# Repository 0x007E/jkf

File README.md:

# `JKF` - JK FlipFlop Board

The `JKF` is a board with an [CD4027](#additional-information) or any other dual `JK-FlipFlop` that meets the pin requirements. The board itself can be driven from `5` to `15V`. The board offers the possibility to create logic circuits driven by buttons, switches or any other logic board.

| Experience  | Level                                                                               |
|:------------|:-----------------------------------------------------------------------------------:|
| Soldering   |  |

# Downloads

| Type      | File                                                                                                                                                 | Description     |
|:---------:|:----------------------------------------------------------------------------------------------------------------------------------------------------:|:----------------|
| Schematic | [pdf](https://github.com/0x007E/jkf/releases/latest/download/schematic.pdf) / [cadlab](https://cadlab.io/project/30131/main/files)                   | Schematic files |
| Board     | [pdf](https://github.com/0x007E/jkf/releases/latest/download/pcb.pdf) / [cadlab](https://cadlab.io/project/30131/main/files)                         | Board file      |
| Drill     | [pdf](https://github.com/0x007E/jkf/releases/latest/download/drill.pdf)                                                                              | Drill file      |
| PCB       | [zip](https://github.com/0x007E/jkf/releases/latest/download/kicad.zip) / [tar](https://github.com/0x007E/jkf/releases/latest/download/kicad.tar.gz) | KiCAD/Gerber/BoM/Drill files |
| Mechanical | [zip](https://github.com/0x007E/jkf/releases/latest/download/freecad.zip) / [tar](https://github.com/0x007E/jkf/releases/latest/download/freecad.tar.gz) | FreeCAD/Housing and exported step/stl files |

# Hardware

The pcb is created with `KiCAD`. All files are built with `github actions` so that they are ready for a production environment.

## PCB

The circuit board is populated on both sides (Top, Bottom). The best way for soldering the `SMD` components is within a vapor phase soldering system and for the `THT` components with a standard soldering system.

### Top Layer

### Bottom Layer

# Additional Information

| Type       | Link                                                  | Description                                 |
|:----------:|:-----------------------------------------------------:|:--------------------------------------------|
| CD4027    | [pdf](https://www.ti.com/lit/ds/symlink/cd4027b.pdf)   | CMOS AND Gate                               |

---

R. GAECHTER

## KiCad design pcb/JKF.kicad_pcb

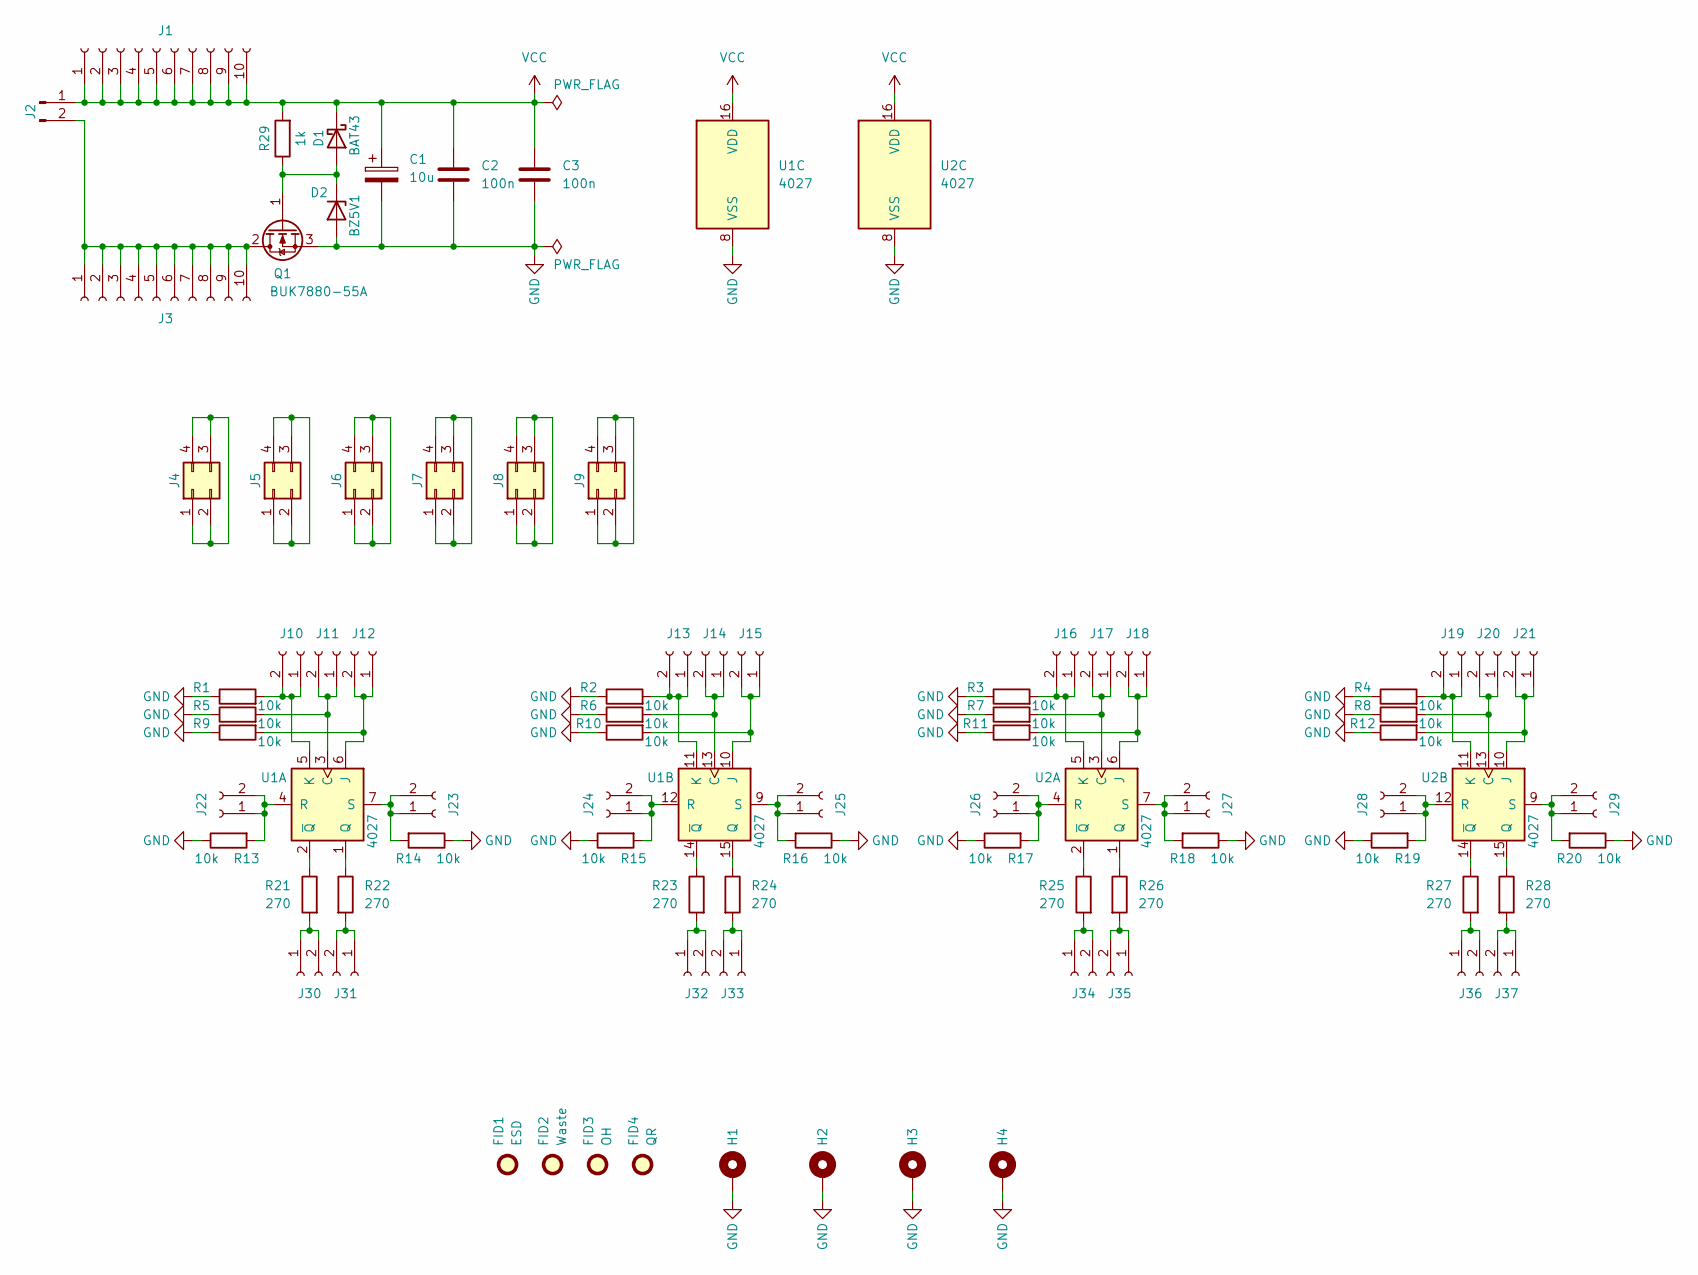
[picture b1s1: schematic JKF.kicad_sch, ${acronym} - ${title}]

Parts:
C1: 10u; CP_Radial_D6.3mm_P2.50mm
C2, C3: 100n; C_1206_3216Metric
D1: BAT43; D_MiniMELF
D2: BZ5V1; D_MiniMELF
FID1: ESD; ESD-Logo_6.6x6mm_SilkScreen
FID2: Waste; WEEE-Logo_4.2x6mm_SilkScreen
FID3: OH; OSHW-Logo_5.7x6mm_SilkScreen
FID4: QR; QR_0x007e
H1, H2, H3, H4: MountingHole_Pad; MountingHole_3.2mm_M3_Pad
J1, J3: Conn_01x10_Socket; PinSocket_1x10_P2.54mm_Vertical
J2: Conn_01x02_Pin; PinHeader_1x02_P2.54mm_Vertical
J4, J5, J6, J7, J8, J9: Conn_02x02_Counter_Clockwise; PinSocket_2x02_P2.54mm_Vertical
J10, J11, J12, J13, J14, J15, J16, J17, J18, J19, J20, J21, J22, J23, J24, J25, J26, J27, J28, J29, J30, J31, J32, J33, J34, J35, J36, J37: Conn_01x02_Socket; PinSocket_1x02_P2.54mm_Vertical
Q1: BUK7880-55A; SOT-223-3_TabPin2
R1, R2, R3, R4, R5, R6, R7, R8, R9, R10, R11, R12, R13, R14, R15, R16, R17, R18, R19, R20: 10k; R_1206_3216Metric
R21, R22, R23, R24, R25, R26, R27, R28: 270; R_1206_3216Metric
R29: 1k; R_1206_3216Metric
U1, U2: 4027; SOIC-16_3.9x9.9mm_P1.27mm

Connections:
GND: C1.2, C2.2, C3.2, D2.2 (A), H1.1, H2.1, H3.1, H4.1, Q1.3 (S), R1.1, R2.1, R3.1, R4.1, R5.1, R6.1, R7.1, R8.1, R9.1, R10.1, R11.1, R12.1, R13.1, R14.1, R15.1, R16.1, R17.1, R18.1, R19.1, R20.1, U1.8 (VSS), U2.8 (VSS)
unnamed: D1.2 (A), D2.1 (K), Q1.1 (G), R29.1
unnamed: J2.2, J3.1, J3.2, J3.3, J3.4, J3.5, J3.6, J3.7, J3.8, J3.9, J3.10, Q1.2 (D)
unnamed: J4.1, J4.2, J4.3, J4.4
unnamed: J5.1, J5.2, J5.3, J5.4
unnamed: J6.1, J6.2, J6.3, J6.4
unnamed: J7.1, J7.2, J7.3, J7.4
unnamed: J8.1, J8.2, J8.3, J8.4
unnamed: J9.1, J9.2, J9.3, J9.4
unnamed: J10.1, J10.2, R1.2, U1.5 (K)
unnamed: J11.1, J11.2, R5.2, U1.3 (C)
unnamed: J12.1, J12.2, R9.2, U1.6 (J)
unnamed: J13.1, J13.2, R2.2, U1.11 (K)
unnamed: J14.1, J14.2, R6.2, U1.13 (C)
unnamed: J15.1, J15.2, R10.2, U1.10 (J)
unnamed: J16.1, J16.2, R3.2, U2.5 (K)
unnamed: J17.1, J17.2, R7.2, U2.3 (C)
unnamed: J18.1, J18.2, R11.2, U2.6 (J)
unnamed: J19.1, J19.2, R4.2, U2.11 (K)
unnamed: J20.1, J20.2, R8.2, U2.13 (C)
unnamed: J21.1, J21.2, R12.2, U2.10 (J)
unnamed: J22.1, J22.2, R13.2, U1.4 (R)
unnamed: J23.1, J23.2, R14.2, U1.7 (S)
unnamed: J24.1, J24.2, R15.2, U1.12 (R)
unnamed: J25.1, J25.2, R16.2, U1.9 (S)
unnamed: J26.1, J26.2, R17.2, U2.4 (R)
unnamed: J27.1, J27.2, R18.2, U2.7 (S)
unnamed: J28.1, J28.2, R19.2, U2.12 (R)
unnamed: J29.1, J29.2, R20.2, U2.9 (S)
unnamed: J30.1, J30.2, R21.2
unnamed: J31.1, J31.2, R22.2
unnamed: J32.1, J32.2, R23.2
unnamed: J33.1, J33.2, R24.2
unnamed: J34.1, J34.2, R25.2
unnamed: J35.1, J35.2, R26.2
unnamed: J36.1, J36.2, R27.2
unnamed: J37.1, J37.2, R28.2
unnamed: R22.1, U1.1 (Q)
unnamed: R21.1, U1.2 (~Q)
unnamed: R24.1, U1.15 (Q)
unnamed: R23.1, U1.14 (~Q)
unnamed: R26.1, U2.1 (Q)
unnamed: R25.1, U2.2 (~Q)
unnamed: R28.1, U2.15 (Q)
unnamed: R27.1, U2.14 (~Q)
VCC: C1.1, C2.1, C3.1, D1.1 (K), J1.1, J1.2, J1.3, J1.4, J1.5, J1.6, J1.7, J1.8, J1.9, J1.10, J2.1, R29.2, U1.16 (VDD), U2.16 (VDD)

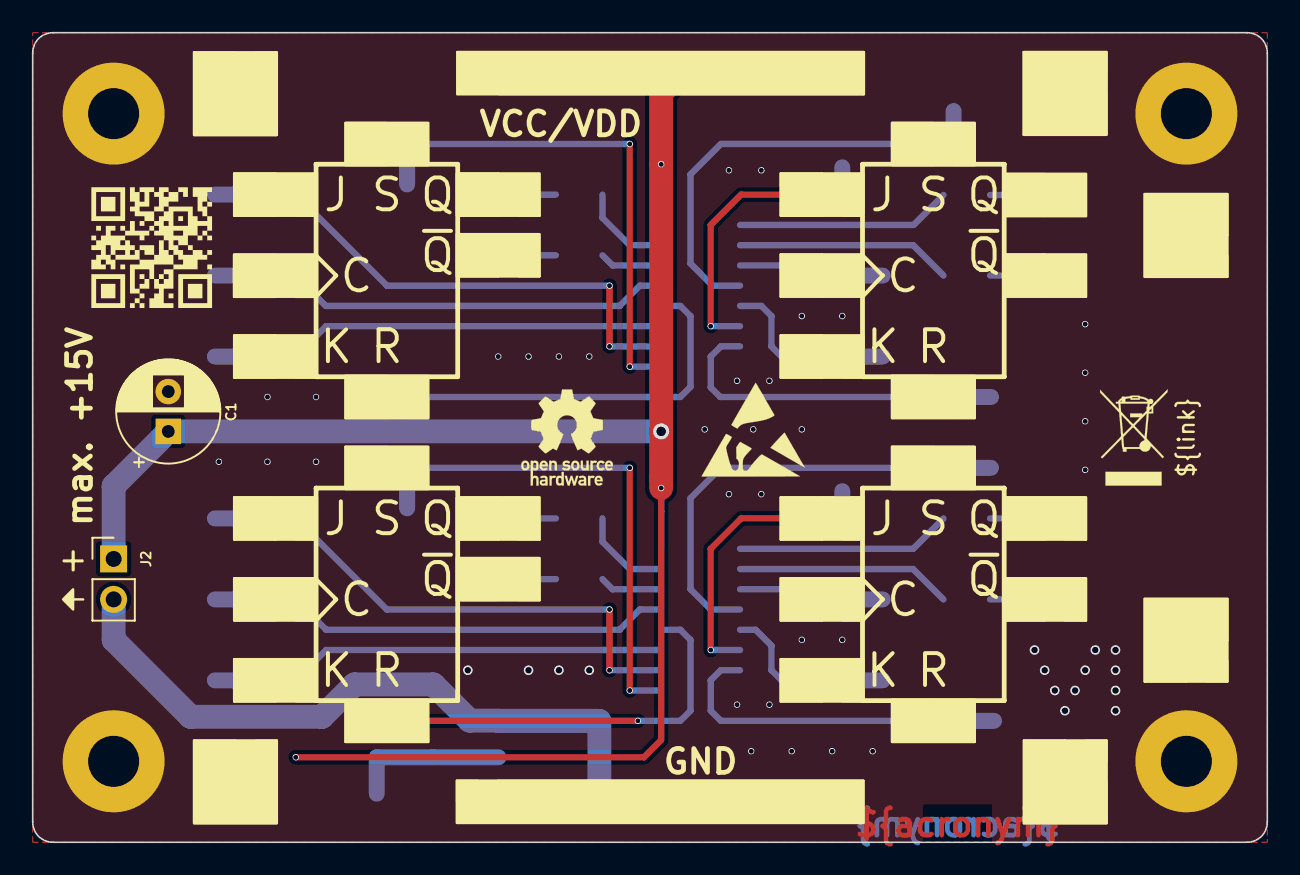
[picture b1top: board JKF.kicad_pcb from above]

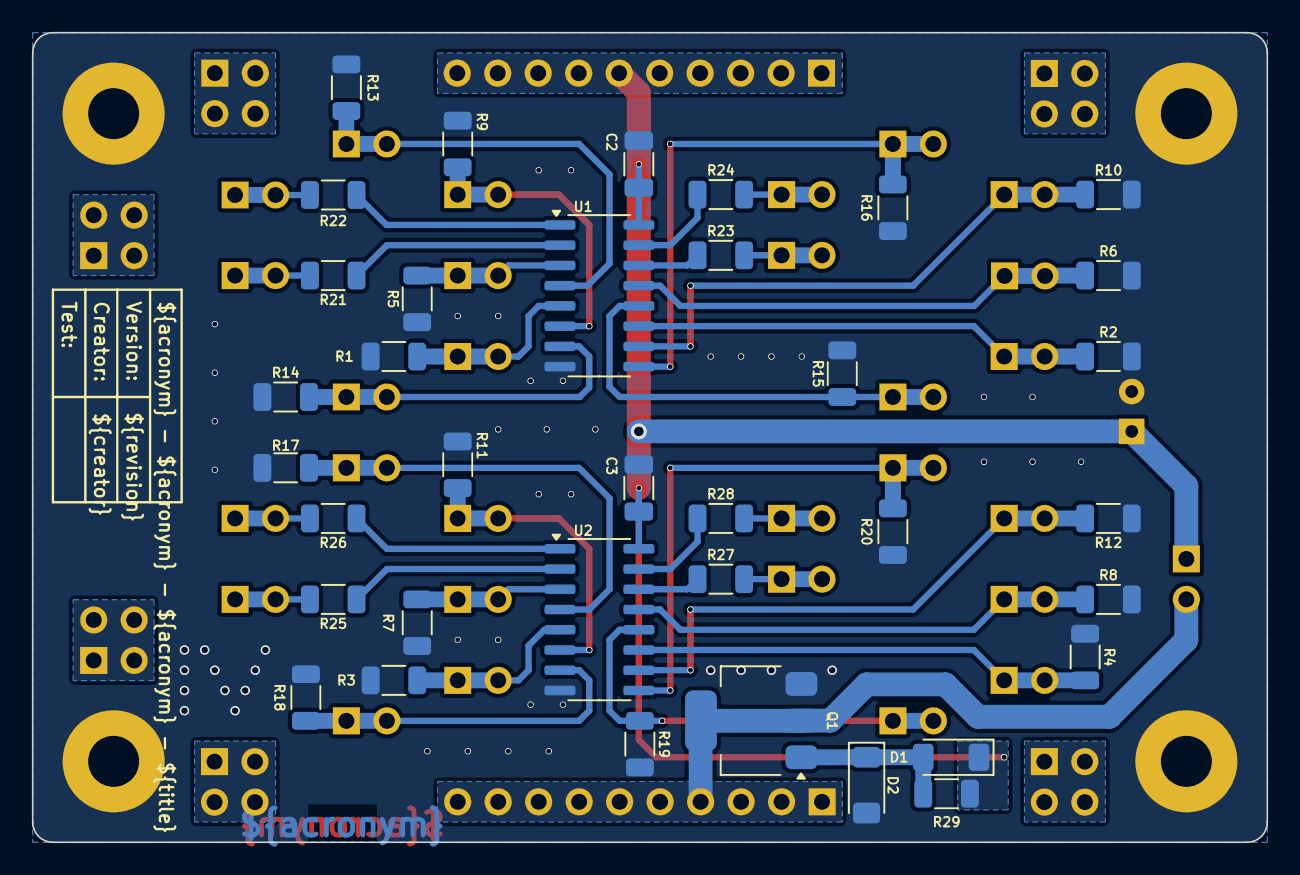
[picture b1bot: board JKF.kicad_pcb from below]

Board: 2 copper layers, 77.5 x 50.8 mm, 82 parts (36 on the bottom side), 46 nets.

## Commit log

2026-03-04 Add pcb layout
2026-03-04 Add README.md
2026-03-04 Add build pipeline
2026-03-04 Add release pipeline
2026-03-09 Remove invalid text
2026-03-23 Adapt edge cuts and dimensioning
2026-03-23 Add FreeCAD modification and export
2026-03-23 Add mechanical download link
2026-05-09 Add reverse polarity protection
2026-05-09 Remove isolated copper filter
2026-05-11 Optimize fabrication layer
2026-05-12 Adapt description

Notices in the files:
README.md:
License CC By-NC-SA
parts and their libraries:
license: CC BY-NC-SA 4.0
